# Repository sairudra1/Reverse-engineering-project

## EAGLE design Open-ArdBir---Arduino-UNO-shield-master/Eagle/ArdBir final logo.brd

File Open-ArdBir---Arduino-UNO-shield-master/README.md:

# Open-ArdBir---Arduino-UNO-shield
Repository for HW design file (PCB, schematic) of ArdBir shield based on arduino UNO version 

Open Ardbir is an open source SW (up to release 2.8.3) to control and automate beer brewing process The SW have been developed based on Arduino UNO board (Atmega328 MCU) with few surroundings HW component to drive and interface external element (PUMP, Heating element , LCD, push button etc.)

There are few open source HW boards available (brauduino like) supporting the SW either designed as shield on top of Arduino Board or stand alone board (all in one board). This repository includes PCB and SCHEMA for the basic Arduino Uno shield 

Enjoy and feel free to modify/fork the project

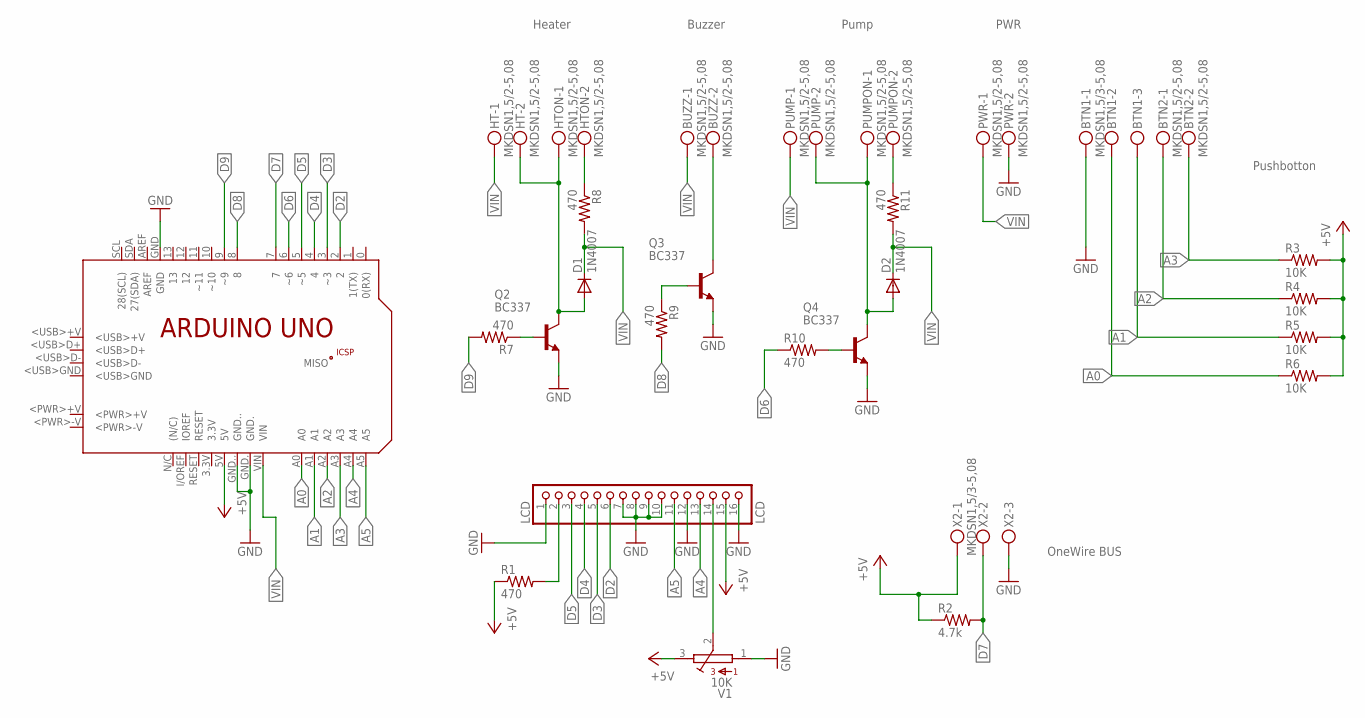
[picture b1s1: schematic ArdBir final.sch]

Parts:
BTN1: MKDSN1,5/3-5,08
BTN2: MKDSN1,5/2-5,08
BUZZ: MKDSN1,5/2-5,08
D1, D2: 1N4007; DO41-10
HT: MKDSN1,5/2-5,08
HTON: MKDSN1,5/2-5,08
LCD: LCD; 1X16
PCB1: ARDUINO_UNO
PUMP: MKDSN1,5/2-5,08
PUMPON: MKDSN1,5/2-5,08
PWR: MKDSN1,5/2-5,08
Q2, Q3, Q4: BC337; TO92
R1, R7, R8, R9, R10, R11: 470; 0207/10
R2: 4.7k; 0207/10
R3, R4, R5, R6: 10K; 0207/10
V1: 10K; CA9V
X2: MKDSN1,5/3-5,08

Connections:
+5V: LCD.15, PCB1.5V, R1.1, R2.1, R3.2, R4.2, R5.2, R6.2, V1.3, X2.1
A0: BTN1.2, PCB1.A0, R6.1
A1: BTN1.3, PCB1.A1, R5.1
A2: BTN2.1, PCB1.A2, R4.1
A3: BTN2.2, PCB1.A3, R3.1
A4: LCD.13, PCB1.A4
A5: LCD.11, PCB1.A5
D2: LCD.6, PCB1.2
D3: LCD.5, PCB1.3 (~3)
D4: LCD.4, PCB1.4
D5: LCD.3, PCB1.5 (~5)
D6: PCB1.6 (~6), R10.1
D7: PCB1.7, R2.2, X2.2
D8: PCB1.8, R9.2
D9: PCB1.9 (~9), R7.2
GND: BTN1.1, LCD.1, LCD.7, LCD.8, LCD.9, LCD.10, LCD.12, LCD.16, PCB1.GND, PCB1.GND., PCB1.GND.., PWR.2, Q2.1 (E), Q3.1 (E), Q4.1 (E), V1.1, X2.3
unnamed: PUMPON.2, R11.1
unnamed: D1.A, HT.2, HTON.1, Q2.3 (C)
unnamed: Q2.2 (B), R7.1
unnamed: LCD.14, V1.2
unnamed: HTON.2, R8.1
unnamed: BUZZ.2, Q3.3 (C)
unnamed: Q3.2 (B), R9.1
unnamed: LCD.2, R1.2
unnamed: Q4.2 (B), R10.2
unnamed: D2.A, PUMP.2, PUMPON.1, Q4.3 (C)
VIN: BUZZ.1, D1.C, D2.C, HT.1, PCB1.VIN, PUMP.1, PWR.1, R8.2, R11.2

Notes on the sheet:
OneWire BUS
Pushbotton
Heater
Buzzer
Pump
PWR

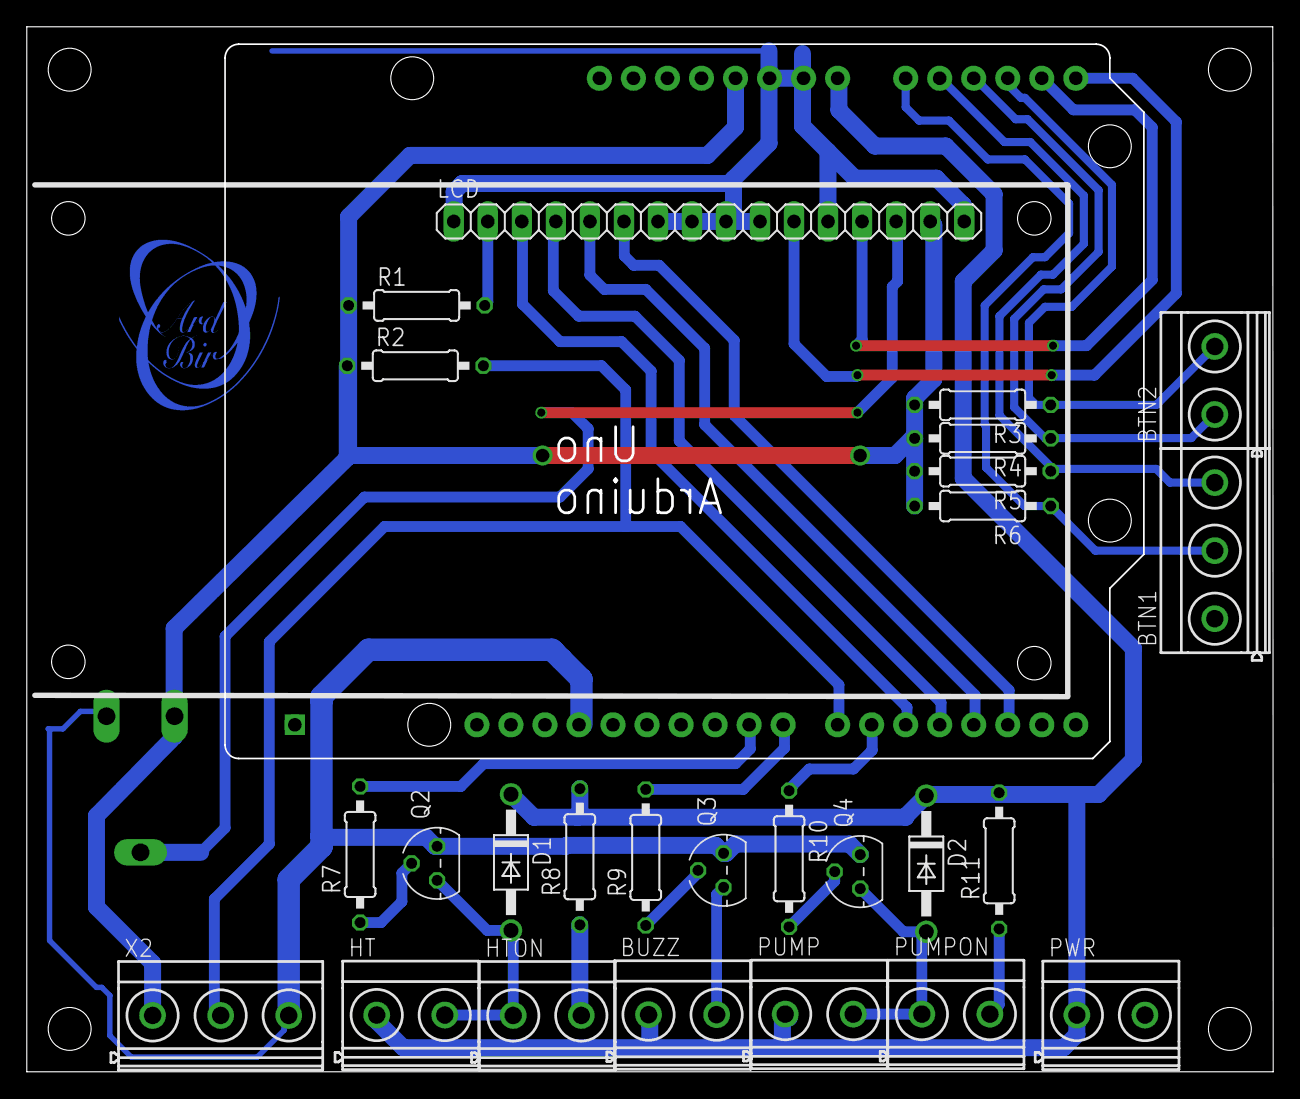
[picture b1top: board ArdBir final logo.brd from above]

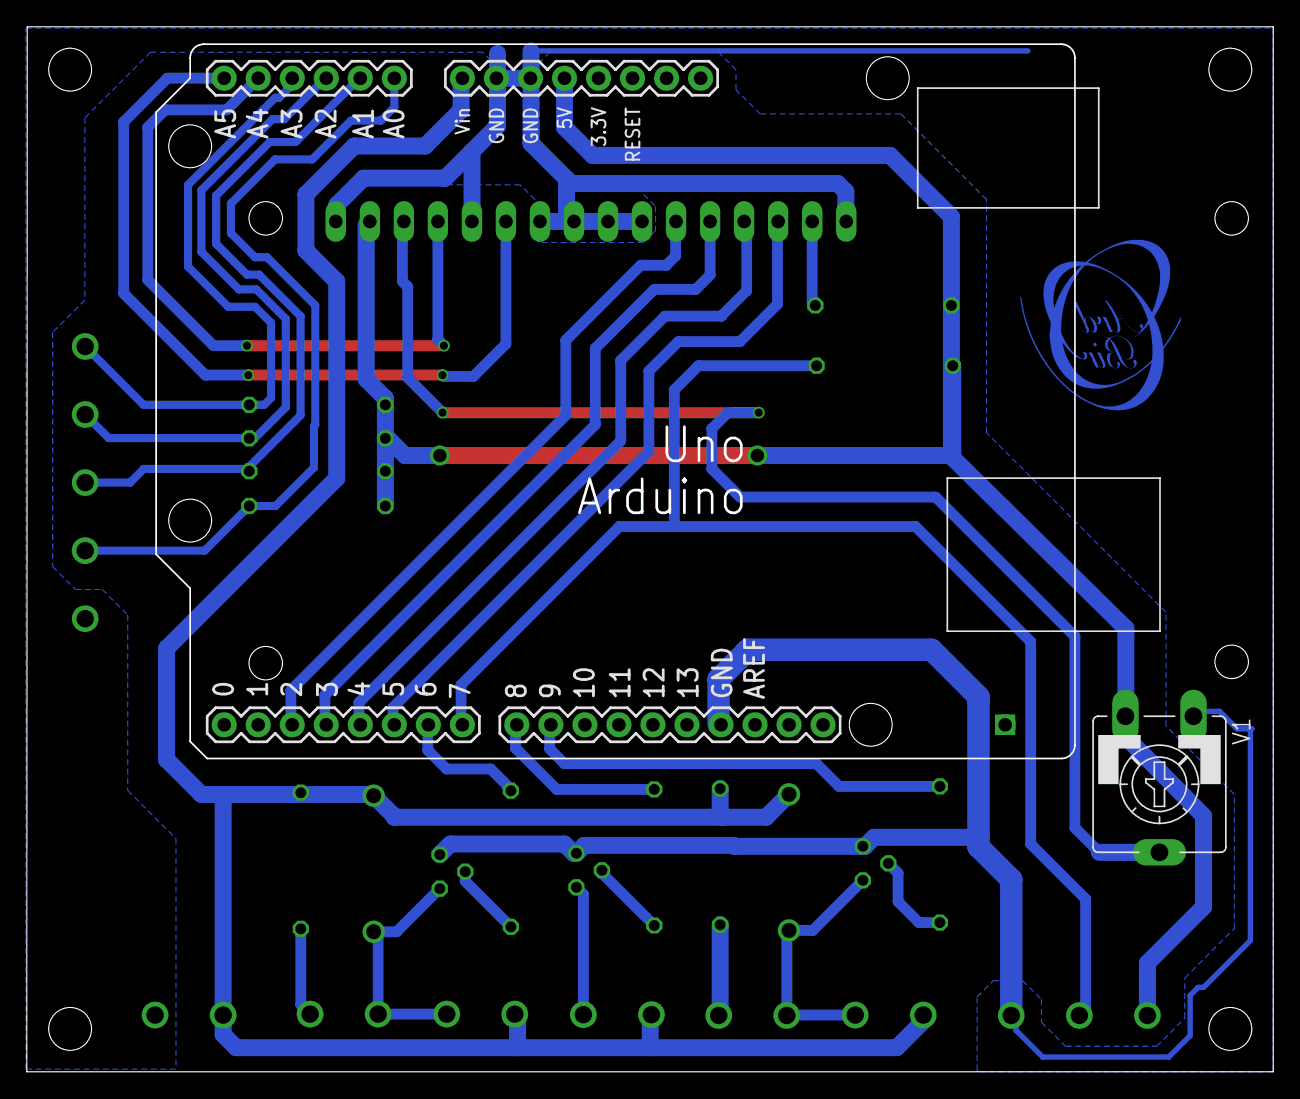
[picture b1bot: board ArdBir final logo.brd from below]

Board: 2 copper layers, 92.9 x 77.9 mm, 28 parts (2 on the bottom side), 27 nets.

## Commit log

2025-11-29 commit 1
2025-11-29 extra redundant
2026-01-19 4 kayer design
